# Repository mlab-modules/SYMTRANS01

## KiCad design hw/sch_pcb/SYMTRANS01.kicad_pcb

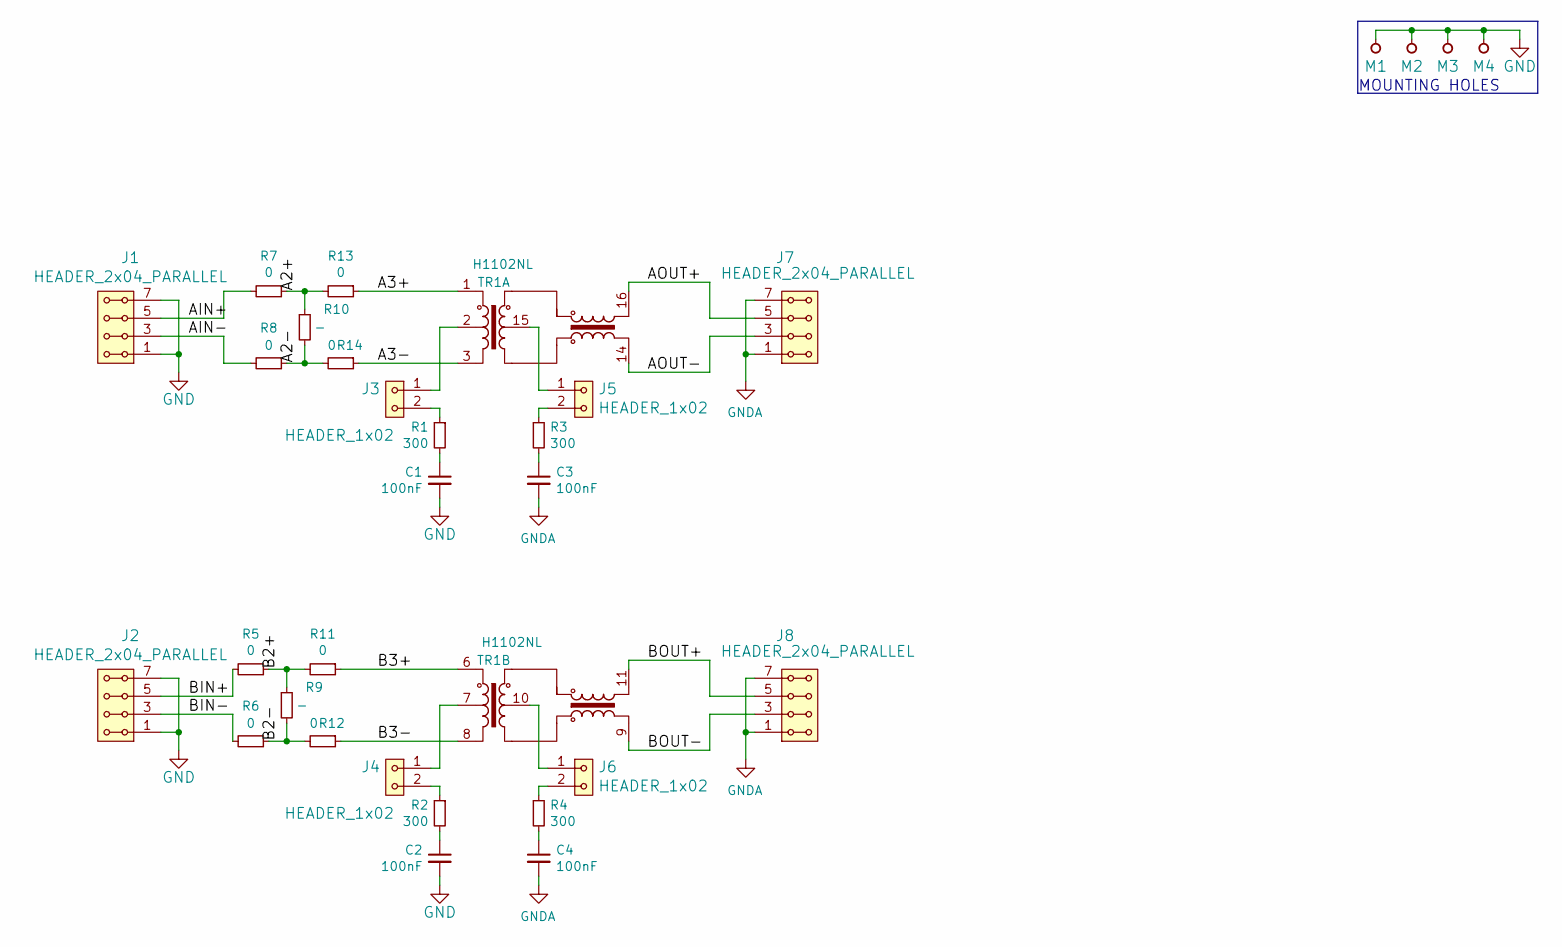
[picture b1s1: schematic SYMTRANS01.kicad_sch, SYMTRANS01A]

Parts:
C1, C2, C3, C4: 100nF; SMD-0805
J1, J2, J7, J8: HEADER_2x04_PARALLEL; Straight_2x04
J3, J4, J5, J6: HEADER_1x02; Straight_2x01
M1, M2, M3, M4: HOLE; MountingHole_3mm
R1, R2, R3, R4: 300; SMD-0805
R5, R6, R7, R8, R11, R12, R13, R14: 0; SMD-0805
R9, R10: -; SMD-0805
TR1: H1102NL; H110X_H1121_HX1188

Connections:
/A2+: R7.1, R10.1, R13.2
/A2-: R8.1, R10.2, R14.2
/A3+: R13.1, TR1.1
/A3-: R14.1, TR1.3
/AIN+: J1.5, J1.6, R7.2
/AIN-: J1.3, J1.4, R8.2
/AOUT+: J7.5, J7.6, TR1.16
/AOUT-: J7.3, J7.4, TR1.14
/B2+: R5.1, R9.1, R11.2
/B2-: R6.1, R9.2, R12.2
/B3+: R11.1, TR1.6
/B3-: R12.1, TR1.8
/BIN+: J2.5, J2.6, R5.2
/BIN-: J2.3, J2.4, R6.2
/BOUT+: J8.5, J8.6, TR1.11
/BOUT-: J8.3, J8.4, TR1.9
GND: C1.2, C2.2, J1.1, J1.2, J1.7, J1.8, J2.1, J2.2, J2.7, J2.8, M1.1, M2.1, M3.1, M4.1
GNDA: C3.2, C4.2, J7.1, J7.2, J7.7, J7.8, J8.1, J8.2, J8.7, J8.8
unnamed: C1.1, R1.2
unnamed: C2.1, R2.2
unnamed: C3.1, R3.2
unnamed: C4.1, R4.2
unnamed: J3.1, TR1.2
unnamed: J3.2, R1.1
unnamed: J4.1, TR1.7
unnamed: J4.2, R2.1
unnamed: J5.1, TR1.15
unnamed: J5.2, R3.1
unnamed: J6.1, TR1.10
unnamed: J6.2, R4.1

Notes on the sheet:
MOUNTING HOLES

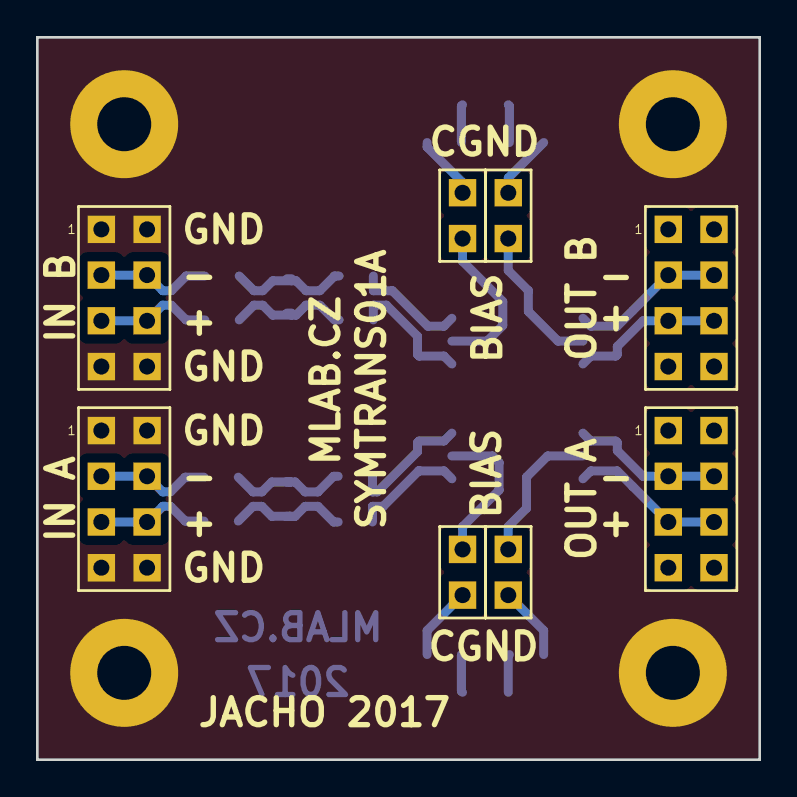
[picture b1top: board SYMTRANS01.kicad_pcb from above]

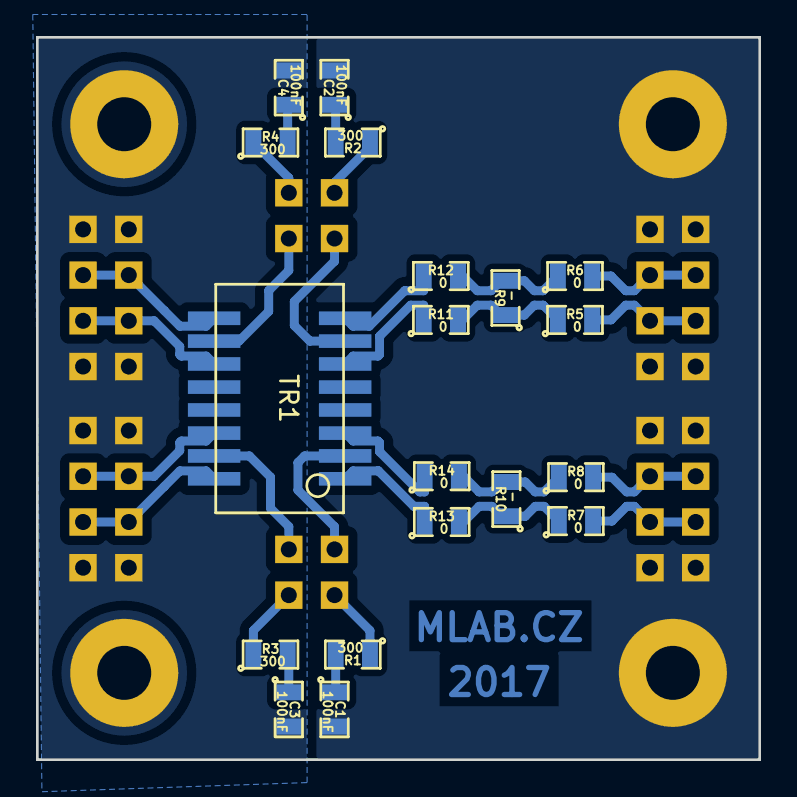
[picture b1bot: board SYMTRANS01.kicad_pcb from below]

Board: 2 copper layers, 40.1 x 40.1 mm, 31 parts (19 on the bottom side), 30 nets.

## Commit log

2023-04-01 Adding force option to enable splitting in not fresh copy of Modules repository.
2023-07-05 automated commit; add github actions
2023-07-05 Update metadata files
2023-07-05 automated commit; rename source files to new naming convence
2023-07-05 Update workflow files
2023-09-16 Update status
2023-09-17 Convert project to KiCAD7.
2023-09-17 Update actions products
